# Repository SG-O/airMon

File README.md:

**WARNING** This is work in progress! Expect everything to be broken!

# airMon - ESP32 based air quality monitor PCB #

## Features ##
### CPU ###
- Standard ESP32 WROOM module
- CH340 based USB to UART
- 802.11 b/g/n
- Bluetooth: v4.2 BR/EDR and BLE

### IO ###
- 1 Analog IO port (0 - 12V)
- 1 Analog IO port (0 - 3.3V)
- 2 I2C buses on 4 connectors (2 of which have switchable power pins)
- 2 Additional buffered I2C connectors for longer cables (using P82B715)
- 8 GPIO
- 1 SW bus
- Dedicated connectors for several particulate matter sensors with switchable power pins
 - SDS011
 - PMS1003 - PMS6003
 - PMS7003
- Input for rainfall, wind speed and direction sensors
- GNSS support (L70/L76/MAX-M8C/MAX-M8Q/MAX-8C/MAX-8Q)
- LoRa support (RFM95/RFM96/RFM97/RFM98/RFM69)
- Input voltage measurement
- JTAG for development

### Power Supply ###
- Wide input range (6 - 35V)
- Ultra-high efficiency at light load
- Capable of 5W combined system load
- Overcurrent protection
- Customizable undervoltage protection (for battery operation)
- Switchable power outputs for high power sensors
- Reverse polarity protection

### Additional features ###
- Fits inside a 75mm waste pipe
- PMS7003 can be directly plugged into the PCB
- Active GNSS Antenna support

## Software ##
This was designed for the Airrohr Firmware developed by Opendata Stuttgart: [https://github.com/opendata-stuttgart/sensors-software/tree/master/airrohr-firmware](https://github.com/opendata-stuttgart/sensors-software/tree/master/airrohr-firmware)

The ESP32 support is currently experimental

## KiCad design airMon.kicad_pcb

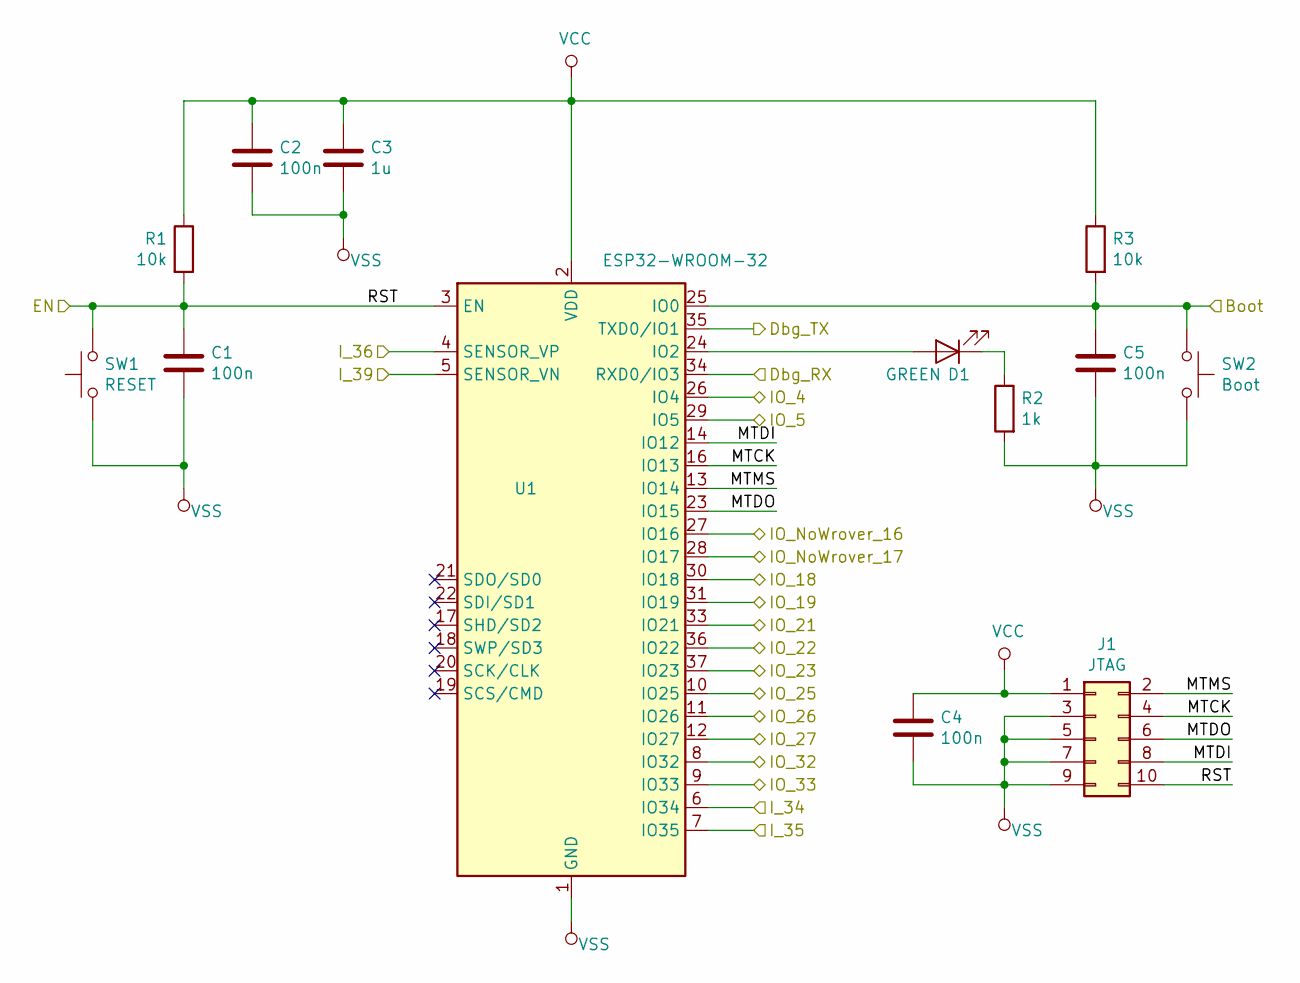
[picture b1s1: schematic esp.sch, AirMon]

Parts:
C1, C2, C4, C5: 100n; C_0603_1608Metric; lcsc# C14663
C3: 1u; C_0805_2012Metric; lcsc# C28323
D1: GREEN; D_0805_2012Metric; lcsc# C2297
J1: JTAG; PinHeader_2x05_P1.27mm_Vertical_SMD; lcsc# C180221
R1, R3: 10k; R_0603_1608Metric; lcsc# C25804
R2: 1k; R_0805_2012Metric; lcsc# C17513
SW1: RESET; SW_SPST_SKQG_WithStem; lcsc# C318889
SW2: Boot; SW_SPST_SKQG_WithStem; lcsc# C318889
U1: ESP32-WROOM-32

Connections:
/A1: U1.6 (IO34); also elsewhere on the board
/A2: U1.7 (IO35); also elsewhere on the board
/A3: U1.4 (SENSOR_VP); also elsewhere on the board
/A4: U1.5 (SENSOR_VN); also elsewhere on the board
/Boot: C5.1, R3.2, SW2.1, U1.25 (IO0); also elsewhere on the board
/EN: C1.1, J1.10, R1.2, SW1.1, U1.3 (EN); also elsewhere on the board
/ESP32/MTCK: J1.4, U1.16 (IO13)
/ESP32/MTDI: J1.8, U1.14 (IO12)
/ESP32/MTDO: J1.6, U1.23 (IO15)
/ESP32/MTMS: J1.2, U1.13 (IO14)
/GPIO_1: U1.37 (IO23); also elsewhere on the board
/GPIO_2: U1.10 (IO25); also elsewhere on the board
/GPIO_3: U1.11 (IO26); also elsewhere on the board
/GPIO_4: U1.12 (IO27); also elsewhere on the board
/GPS_Wake: U1.29 (IO5); also elsewhere on the board
/SCL_1: U1.36 (IO22); also elsewhere on the board
/SCL_2: U1.31 (IO19); also elsewhere on the board
/SDA_1: U1.33 (IO21); also elsewhere on the board
/SDA_2: U1.30 (IO18); also elsewhere on the board
/SW_BUS: U1.26 (IO4); also elsewhere on the board
/U1_RX: U1.8 (IO32); also elsewhere on the board
/U1_TX: U1.9 (IO33); also elsewhere on the board
/U2_RX: U1.27 (IO16); also elsewhere on the board
/U2_TX: U1.28 (IO17); also elsewhere on the board
/U3_RX: U1.34 (RXD0/IO3); also elsewhere on the board
/U3_TX: U1.35 (TXD0/IO1); also elsewhere on the board
unnamed: D1.1 (K), R2.1
unnamed: D1.2 (A), U1.24 (IO2)
VCC: C2.1, C3.1, C4.1, J1.1, R1.1, R3.1, U1.2 (VDD); also elsewhere on the board
VSS: C1.2, C2.2, C3.2, C4.2, C5.2, J1.3, J1.5, J1.7, J1.9, R2.2, SW1.2, SW2.2, U1.1 (GND), U1.15 (GND), U1.38 (GND), U1.39 (GND); also elsewhere on the board

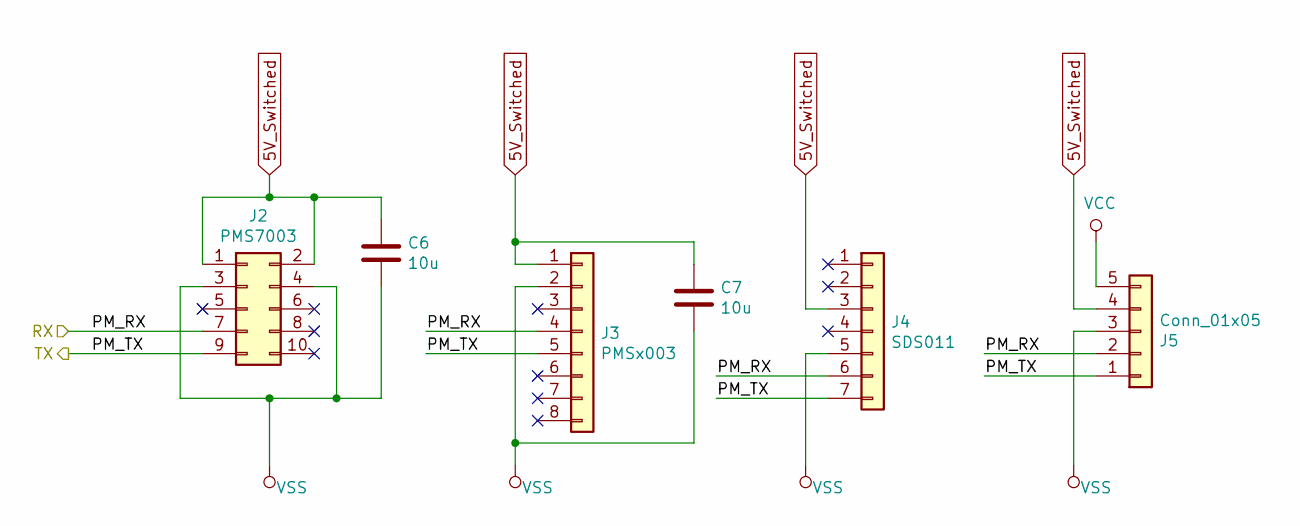
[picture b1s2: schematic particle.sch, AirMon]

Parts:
C6, C7: 10u; C_1206_3216Metric; lcsc# C13585
J2: PMS7003; PinSocket_2x05_P1.27mm_Vertical
J3: PMSx003; Molex_PicoBlade_53047-0810_1x08_P1.25mm_Vertical; lcsc# C240845
J4: SDS011; JST_XH_B07B-XH-A_1x07_P2.50mm_Vertical; lcsc# C144398
J5: Conn_01x05; JST_XH_B05B-XH-A_1x05_P2.50mm_Vertical; lcsc# C157991

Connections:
5V_Switched: C6.1, C7.1, J2.1, J2.2, J3.1, J4.3, J5.4; also elsewhere on the board
/U1_RX: J2.9, J3.5, J4.7, J5.1; also elsewhere on the board
/U1_TX: J2.7, J3.4, J4.6, J5.2; also elsewhere on the board
VCC: J5.5; also elsewhere on the board
VSS: C6.2, C7.2, J2.3, J2.4, J3.2, J4.5, J5.3; also elsewhere on the board

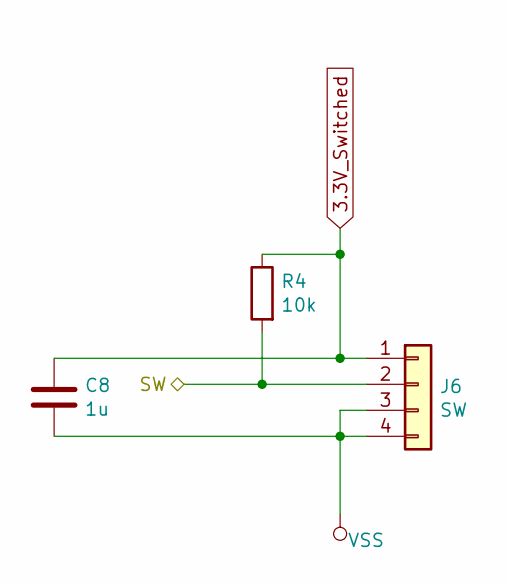
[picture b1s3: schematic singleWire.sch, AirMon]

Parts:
C8: 1u; C_0805_2012Metric; lcsc# C28323
J6: SW; PinSocket_1x04_P2.54mm_Vertical
R4: 10k; R_0603_1608Metric; lcsc# C25804

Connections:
3.3V_Switched: C8.1, J6.1, R4.1; also elsewhere on the board
/SW_BUS: J6.2, R4.2; also elsewhere on the board
VSS: C8.2, J6.3, J6.4; also elsewhere on the board

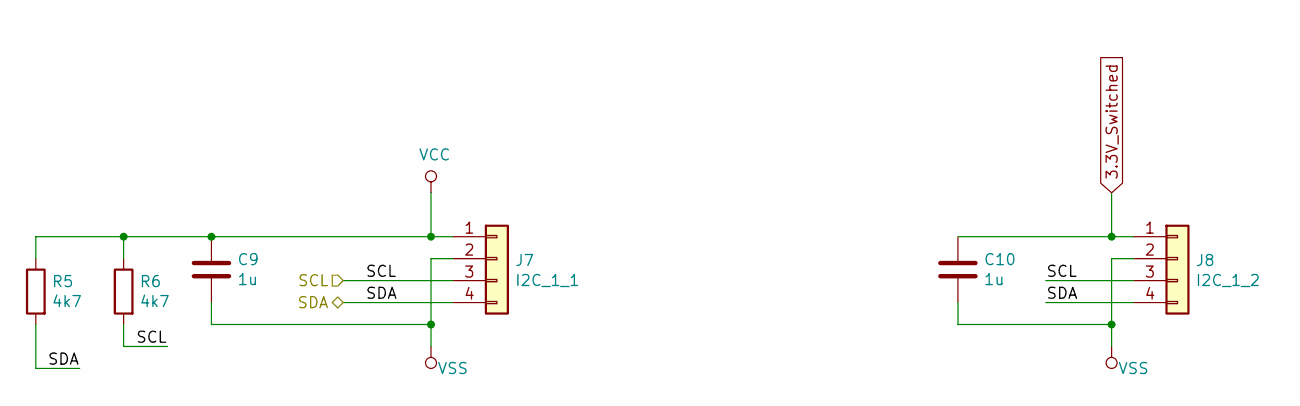
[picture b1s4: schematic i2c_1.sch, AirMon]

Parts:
C9, C10: 1u; C_0805_2012Metric; lcsc# C28323
J7: I2C_1_1; PinSocket_1x04_P2.54mm_Vertical
J8: I2C_1_2; PinSocket_1x04_P2.54mm_Vertical
R5, R6: 4k7; R_0603_1608Metric; lcsc# C23162

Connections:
3.3V_Switched: C10.1, J8.1; also elsewhere on the board
/SCL_1: J7.3, J8.3, R6.2; also elsewhere on the board
/SDA_1: J7.4, J8.4, R5.2; also elsewhere on the board
VCC: C9.1, J7.1, R5.1, R6.1; also elsewhere on the board
VSS: C9.2, C10.2, J7.2, J8.2; also elsewhere on the board

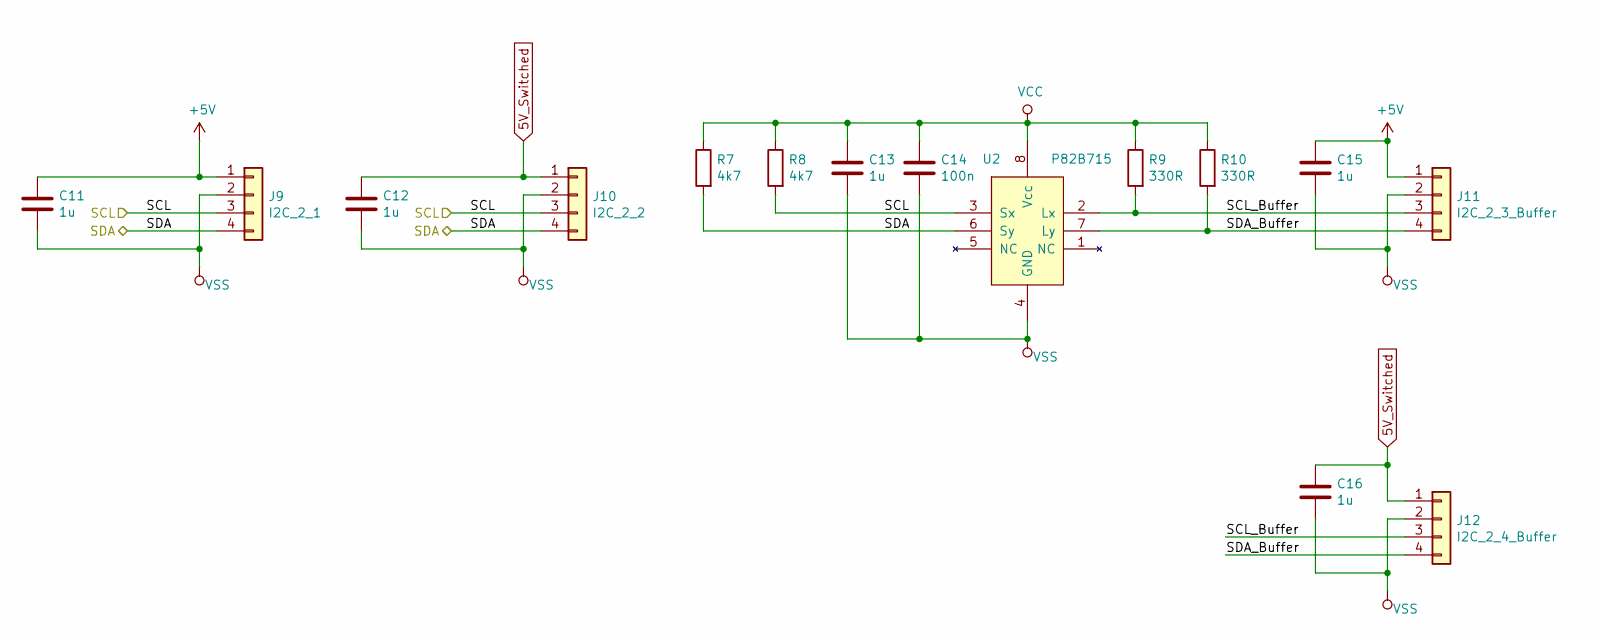
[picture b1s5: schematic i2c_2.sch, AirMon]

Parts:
C11, C12, C13, C15, C16: 1u; C_0805_2012Metric; lcsc# C28323
C14: 100n; C_0603_1608Metric; lcsc# C14663
J9: I2C_2_1; PinSocket_1x04_P2.54mm_Vertical
J10: I2C_2_2; PinSocket_1x04_P2.54mm_Vertical
J11: I2C_2_3_Buffer; PinSocket_1x04_P2.54mm_Vertical
J12: I2C_2_4_Buffer; PinSocket_1x04_P2.54mm_Vertical
R7, R8: 4k7; R_0603_1608Metric; lcsc# C23162
R9, R10: 330R; R_0603_1608Metric; lcsc# C23138
U2: P82B715; SOIC-8_3.9x4.9mm_P1.27mm; digikey# 296-24729-1-ND

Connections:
5V_Switched: C12.1, C16.1, J10.1, J12.1; also elsewhere on the board
+5V: C11.1, C15.1, J9.1, J11.1; also elsewhere on the board
/I2C_2/SCL_Buffer: J11.3, J12.3, R9.2, U2.2 (Lx)
/I2C_2/SDA_Buffer: J11.4, J12.4, R10.2, U2.7 (Ly)
/SCL_2: J9.3, J10.3, R8.2, U2.3 (Sx); also elsewhere on the board
/SDA_2: J9.4, J10.4, R7.2, U2.6 (Sy); also elsewhere on the board
VCC: C13.1, C14.1, R7.1, R8.1, R9.1, R10.1, U2.8 (Vcc); also elsewhere on the board
VSS: C11.2, C12.2, C13.2, C14.2, C15.2, C16.2, J9.2, J10.2, J11.2, J12.2, U2.4 (GND); also elsewhere on the board

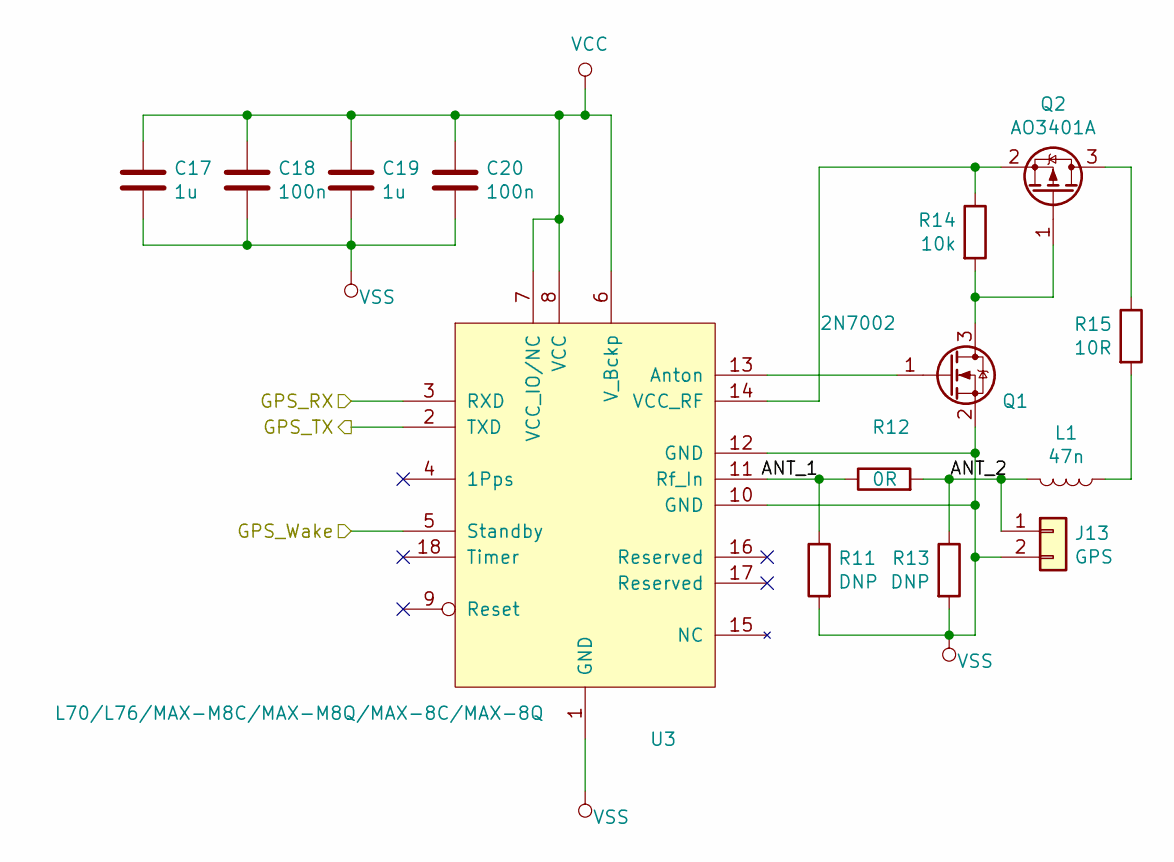
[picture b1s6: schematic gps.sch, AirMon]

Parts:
C17, C19: 1u; C_0805_2012Metric; lcsc# C28323
C18, C20: 100n; C_0603_1608Metric; lcsc# C14663
J13: GPS; U.FL_Molex_MCRF_73412-0110_Vertical; lcsc# C88374
L1: 47n; L_0603_1608Metric; lcsc# C29683
Q1: 2N7002; SOT-23; lcsc# C8545
Q2: AO3401A; SOT-23; lcsc# C15127
R11, R13: DNP; R_0603_1608Metric
R12: 0R; R_0603_1608Metric; lcsc# C21189
R14: 10k; R_0603_1608Metric; lcsc# C25804
R15: 10R; R_0603_1608Metric; lcsc# C22859
U3: L70/L76/MAX-M8C/MAX-M8Q/MAX-8C/MAX-8Q; L70

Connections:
/GPS/ANT_1: R11.1, R12.1, U3.11 (Rf_In)
/GPS/ANT_2: J13.1, L1.2, R12.2, R13.1
/GPS_Wake: U3.5 (Standby); also elsewhere on the board
/U2_RX: U3.2 (TXD); also elsewhere on the board
/U2_TX: U3.3 (RXD); also elsewhere on the board
unnamed: L1.1, R15.2
unnamed: Q1.1 (G), U3.13 (Anton)
unnamed: Q1.3 (D), Q2.1 (G), R14.2
unnamed: Q2.2 (S), R14.1, U3.14 (VCC_RF)
unnamed: Q2.3 (D), R15.1
VCC: C17.1, C18.1, C19.1, C20.1, U3.6 (V_Bckp), U3.7 (VCC_IO/NC), U3.8 (VCC); also elsewhere on the board
VSS: C17.2, C18.2, C19.2, C20.2, J13.2, Q1.2 (S), R11.2, R13.2, U3.1 (GND), U3.10 (GND), U3.12 (GND); also elsewhere on the board

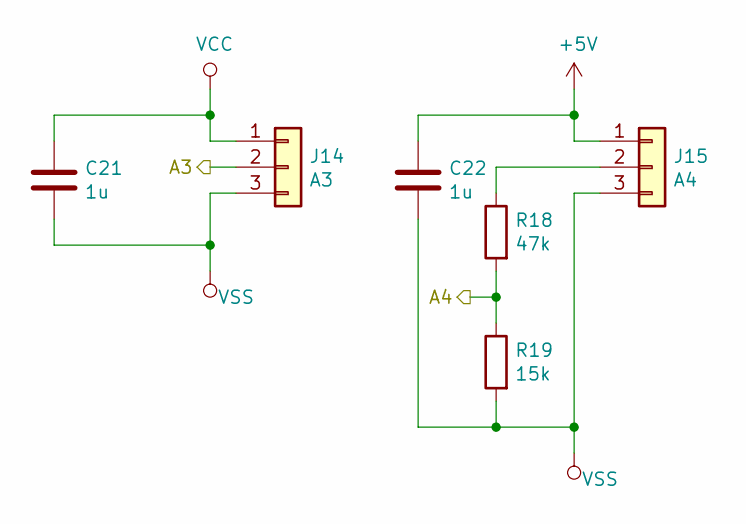
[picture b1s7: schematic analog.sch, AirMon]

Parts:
C21, C22: 1u; C_0805_2012Metric; lcsc# C28323
J14: A3; PinSocket_1x03_P2.54mm_Vertical
J15: A4; PinSocket_1x03_P2.54mm_Vertical
R18: 47k; R_0603_1608Metric; lcsc# C25819
R19: 15k; R_0603_1608Metric; lcsc# C22809

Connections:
+5V: C22.1, J15.1; also elsewhere on the board
/A3: J14.2; also elsewhere on the board
/A4: R18.2, R19.1; also elsewhere on the board
unnamed: J15.2, R18.1
VCC: C21.1, J14.1; also elsewhere on the board
VSS: C21.2, C22.2, J14.3, J15.3, R19.2; also elsewhere on the board

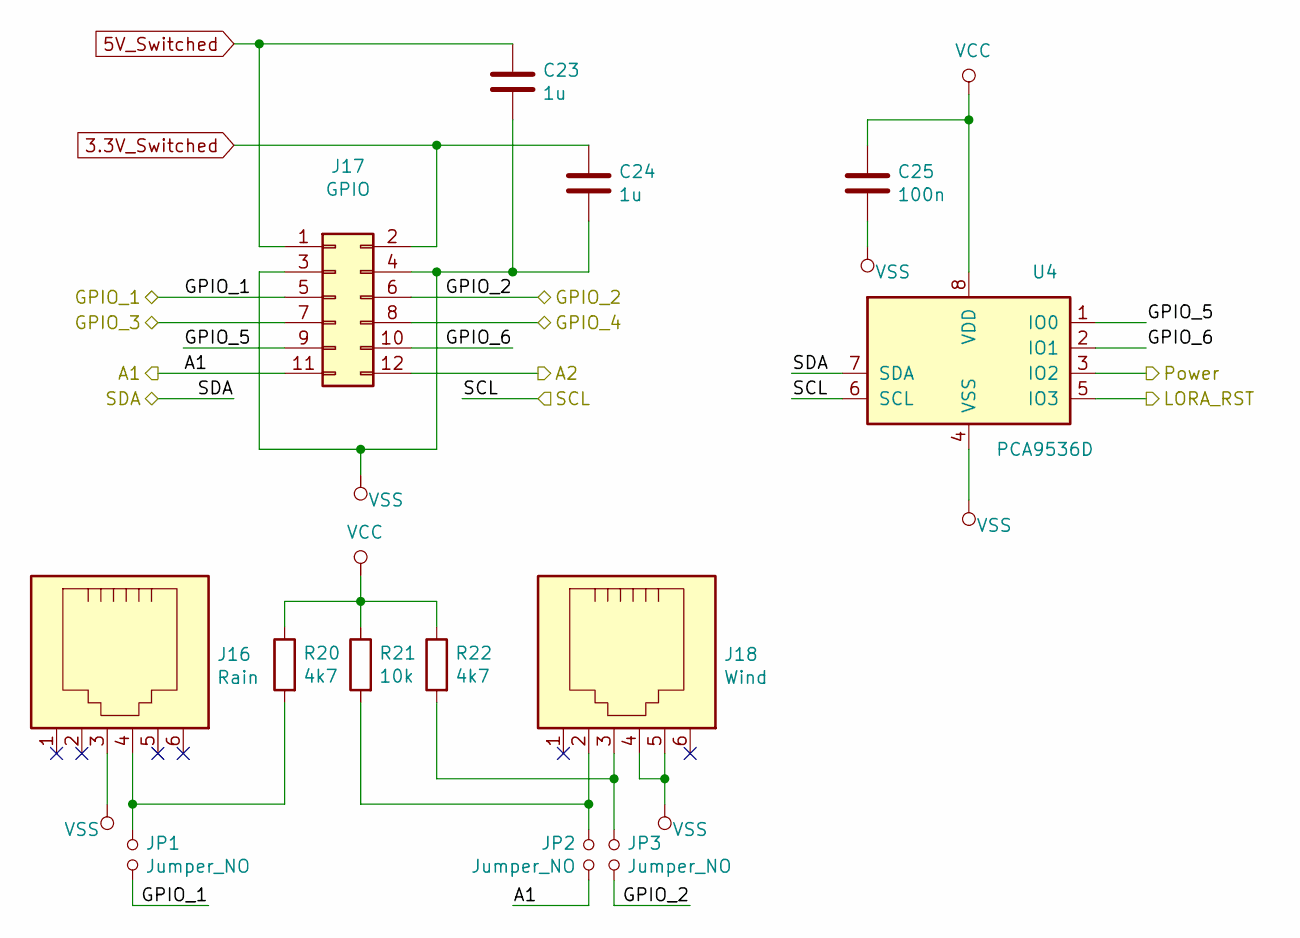
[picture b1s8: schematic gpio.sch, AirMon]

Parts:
C23, C24: 1u; C_0805_2012Metric; lcsc# C28323
C25: 100n; C_0603_1608Metric; lcsc# C14663
J16: Rain; DS1133-S60; lcsc# C77856
J17: GPIO; PinHeader_2x06_P2.54mm_Vertical
J18: Wind; DS1133-S60; lcsc# C77856
JP1, JP2, JP3: Jumper_NO; PinHeader_1x02_P2.54mm_Vertical
R20, R22: 4k7; R_0603_1608Metric; lcsc# C23162
R21: 10k; R_0603_1608Metric; lcsc# C25804
U4: PCA9536D; SOIC-8_3.9x4.9mm_P1.27mm; lcsc# C129522

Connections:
3.3V_Switched: C24.1, J17.2; also elsewhere on the board
5V_Switched: C23.1, J17.1; also elsewhere on the board
/A1: J17.11, JP2.2; also elsewhere on the board
/A2: J17.12; also elsewhere on the board
/GPIO/GPIO_5: J17.9, U4.1 (IO0)
/GPIO/GPIO_6: J17.10, U4.2 (IO1)
/GPIO_1: J17.5, JP1.2; also elsewhere on the board
/GPIO_2: J17.6, JP3.2; also elsewhere on the board
/GPIO_3: J17.7; also elsewhere on the board
/GPIO_4: J17.8; also elsewhere on the board
/LORA_RST: U4.5 (IO3); also elsewhere on the board
/POWER: U4.3 (IO2); also elsewhere on the board
/SCL_1: U4.6 (SCL); also elsewhere on the board
/SDA_1: U4.7 (SDA); also elsewhere on the board
unnamed: J16.4, JP1.1, R20.2
unnamed: J18.2, JP2.1, R21.2
unnamed: J18.3, JP3.1, R22.2
VCC: C25.1, R20.1, R21.1, R22.1, U4.8 (VDD); also elsewhere on the board
VSS: C23.2, C24.2, C25.2, J16.3, J17.3, J17.4, J18.4, J18.5, U4.4 (VSS); also elsewhere on the board

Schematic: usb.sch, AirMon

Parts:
C26: 10u; C_1206_3216Metric; lcsc# C13585
C27, C28: 100n; C_0603_1608Metric; lcsc# C14663
F1: Polyfuse; Fuse_0603_1608Metric; lcsc# C207014
J19: USB_B_Micro; USB_Micro-B_Molex-105017-0001; lcsc# C136000
Q3, Q4: SS8050; SOT-23; lcsc# C2150
R23, R24: 470R; R_0603_1608Metric; lcsc# C23179
R25, R26: 10k; R_0603_1608Metric; lcsc# C25804
U5: CH340C; SOIC-16_3.9x9.9mm_P1.27mm; lcsc# C84681

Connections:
/Boot: Q4.3 (C); also elsewhere on the board
/EN: Q3.3 (C); also elsewhere on the board
/U3_RX: R24.2; also elsewhere on the board
/U3_TX: R23.2; also elsewhere on the board
/USB/DTR: Q4.2 (E), R25.1, U5.13 (~DTR)
/USB/RTS: Q3.2 (E), R26.1, U5.14 (~RTS)
unnamed: C26.1, F1.2, J19.1 (VBUS)
unnamed: C27.1, U5.4 (V3)
unnamed: J19.2 (D-), U5.6 (UD-)
unnamed: J19.3 (D+), U5.5 (UD+)
unnamed: Q3.1 (B), R25.2
unnamed: Q4.1 (B), R26.2
unnamed: R23.1, U5.3 (RXD)
unnamed: R24.1, U5.2 (TXD)
VBUS: F1.1; also elsewhere on the board
VCC: C28.1, U5.16 (VCC); also elsewhere on the board
VSS: C26.2, C27.2, C28.2, J19.5 (GND), J19.6 (Shield), U5.1 (GND); also elsewhere on the board

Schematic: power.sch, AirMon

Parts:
C29, C31, C32, C34: 10u; C_1206_3216Metric; lcsc# C13585
C30, C33: 100n; C_0603_1608Metric; lcsc# C14663
D2, D5: SK36A-LTP; D_SMA; digikey# SK36A-LTPMSCT-ND
D3, D4: BAT760-7; D_SOD-323; lcsc# C124187
D6: UDZVTE-1712B; D_SOD-323F; lcsc# C84980
J20: Power; TerminalBlock_bornier-2_P5.08mm; lcsc# C8475
JP4: Jumper_NO; PinHeader_1x02_P2.54mm_Vertical
L2: 22uH; L_Bourns_SRN8040; digikey# SRN8040-220MCT-ND
L3: 15uH; L_Bourns_SRN6045TA; digikey# SRN6045-150MCT-ND
Q5, Q7: 2N7002; SOT-23; lcsc# C8545
Q6, Q8, Q9: DMP6023LE-13; SOT-223-3_TabPin2; lcsc# C154901
R27, R28: DNP; R_Axial_DIN0204_L3.6mm_D1.6mm_P7.62mm_Horizontal
R29, R34, R36: 110k; R_0603_1608Metric; lcsc# C326736
R30, R32, R33: 100k; R_0603_1608Metric; lcsc# C25803
R31: 10k; R_0603_1608Metric; lcsc# C25804
R35: 20k; R_0603_1608Metric; lcsc# C191225
R37: 33k; R_0603_1608Metric; lcsc# C416700
R38: 1M; R_0603_1608Metric; lcsc# C22935
U6, U7: LMR14010ADDCR; TSOT-23-6; lcsc# C388174

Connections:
3.3V_Switched: Q8.2 (D); also elsewhere on the board
5V_Switched: Q6.2 (D); also elsewhere on the board
+5V: C31.1, D4.2 (A), L2.1, Q6.3 (S), R30.1, R34.1; also elsewhere on the board
+VDC: C29.1, D6.1 (K), Q9.3 (S), R27.1, R29.1, U6.5 (VIN)
/A3: JP4.1; also elsewhere on the board
/POWER: Q5.1 (G), Q7.1 (G), R32.2; also elsewhere on the board
unnamed: C30.1, U6.1 (CB)
unnamed: C30.2, D2.1 (K), L2.2, U6.6 (SW)
unnamed: C32.1, D3.1 (K), D4.1 (K), U7.4 (~SHDN), U7.5 (VIN)
unnamed: C33.1, U7.1 (CB)
unnamed: C33.2, D5.1 (K), L3.2, U7.6 (SW)
unnamed: D6.2 (A), Q9.1 (G), R38.1
unnamed: J20.1, Q9.2 (D)
unnamed: JP4.2, R29.2, R31.1
unnamed: Q5.3 (D), Q6.1 (G), R30.2
unnamed: Q7.3 (D), Q8.1 (G), R33.2
unnamed: R27.2, R28.1, U6.4 (~SHDN)
unnamed: R34.2, R35.1, U6.3 (FB)
unnamed: R36.2, R37.1, U7.3 (FB)
VBUS: D3.2 (A); also elsewhere on the board
VCC: C34.1, L3.1, Q8.3 (S), R33.1, R36.1; also elsewhere on the board
VSS: C29.2, C31.2, C32.2, C34.2, D2.2 (A), D5.2 (A), J20.2, Q5.2 (S), Q7.2 (S), R28.2, R31.2, R32.1, R35.2, R37.2, R38.2, U6.2 (GND), U7.2 (GND); also elsewhere on the board

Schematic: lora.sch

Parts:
C35: 1u; C_0805_2012Metric; lcsc# C28323
J21: LORA_1; U.FL_Molex_MCRF_73412-0110_Vertical; lcsc# C88374
J22: LORA_2; PinHeader_1x02_P1.27mm_Vertical
JP5: Mode; SolderJumper-3_P1.3mm_Bridged12_RoundedPad1.0x1.5mm_NumberL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
R39, R41: DNP; R_0603_1608Metric
R40: 0R; R_0603_1608Metric; lcsc# C21189
U8: RFM95W-868S2; HOPERF_RFM9XW_SMD

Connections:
/A1: U8.14 (DIO0); also elsewhere on the board
/A2: JP5.2 (C); also elsewhere on the board
/GPIO_1: U8.3 (MOSI); also elsewhere on the board
/GPIO_2: U8.2 (MISO); also elsewhere on the board
/GPIO_3: U8.4 (SCK); also elsewhere on the board
/GPIO_4: U8.5 (NSS); also elsewhere on the board
/LORA/ANT_1: R39.1, R40.1, U8.9 (ANT)
/LORA/ANT_2: J21.1, J22.1, R40.2, R41.1
/LORA_RST: U8.6 (RESET); also elsewhere on the board
unnamed: JP5.1 (A), U8.15 (DIO1)
unnamed: JP5.3 (B), U8.16 (DIO2)
VCC: C35.1, U8.13 (3.3V); also elsewhere on the board
VSS: C35.2, J21.2, J22.2, R39.2, R41.2, U8.1 (GND), U8.8 (GND), U8.10 (GND); also elsewhere on the board

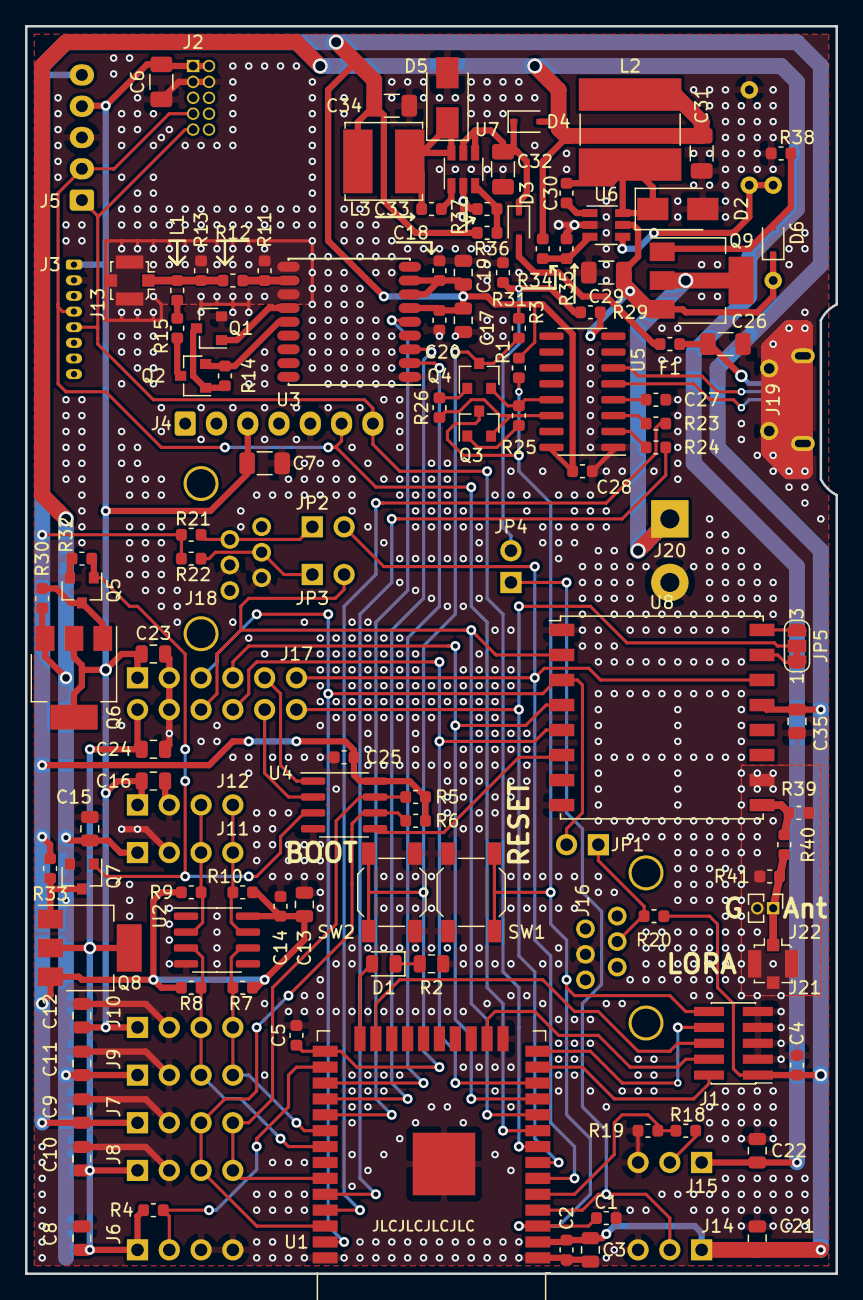
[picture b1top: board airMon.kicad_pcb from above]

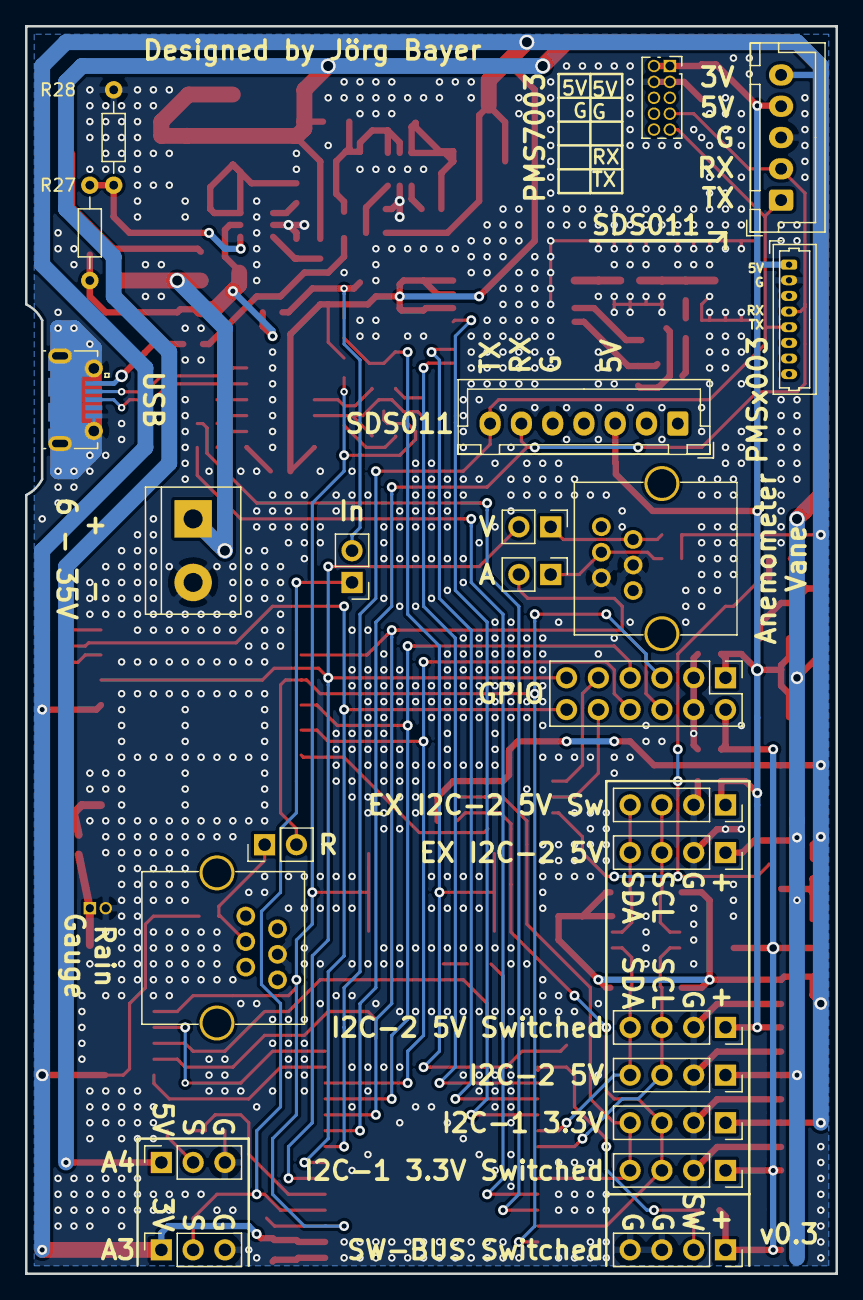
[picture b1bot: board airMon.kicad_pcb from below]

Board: 2 copper layers, 64.8 x 99.7 mm, 130 parts (24 on the bottom side), 79 nets.

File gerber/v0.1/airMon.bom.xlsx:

Comment | Designator | Footprint | LCSC Part #（optional）
100n | C1 C2 C4 C5 C14 C18 C20 C25 C27 C28 C30 C33 | C_0603_1608Metric | C14663
10u | C6 C7 C26 C29 C31 C32 C34 | C_1206_3216Metric | C13585
1u | C3 C8 C9 C10 C11 C12 C13 C15 C16 C17 C19 C21 C22 C23 C24 | C_0805_2012Metric | C28323
BAT760-7 | D3 D4 | D_SOD-323 | C124187
GREEN | D1 | D_0805_2012Metric | C2297
UDZVTE-1712B | D6 | D_SOD-323F | C84980
Polyfuse | F1 | Fuse_0603_1608Metric | C207014
Conn_01x05 | J5 | JST_XH_B05B-XH-A_1x05_P2.50mm_Vertical | C157991
GPS | J13 | U.FL_Molex_MCRF_73412-0110_Vertical | C88374
PMSx003 | J3 | Molex_PicoBlade_53047-0810_1x08_P1.25mm_Vertical | C240845
Power | J20 | TerminalBlock_bornier-2_P5.08mm | C8475
Rain | J16 | DS1133-S60 | C77856
SDS011 | J4 | JST_XH_B07B-XH-A_1x07_P2.50mm_Vertical | C144398
USB_B_Micro | J19 | USB_Micro-B_Molex-105017-0001 | C136000
Wind | J18 | DS1133-S60 | C77856
47n | L1 | L_0603_1608Metric | C29683
2N7002 | Q1 Q5 Q7 | SOT-23 | C8545
AO3401A | Q2 | SOT-23 | C15127
DMP6023LE-13 | Q6 Q8 Q9 | SOT-223-3_TabPin2 | C154901
SS8050 | Q3 Q4 | SOT-23 | C2150
0R | R12 | R_0603_1608Metric | C21189
100k | R30 R32 R33 | R_0603_1608Metric | C25803
10R | R15 | R_0603_1608Metric | C22859
10k | R1 R3 R4 R14 R21 R25 R26 R31 | R_0603_1608Metric | C25804
110k | R29 R34 R36 | R_0603_1608Metric | C326736
15k | R17 R19 | R_0603_1608Metric | C22809
1M | R38 | R_0603_1608Metric | C22935
1k | R2 | R_0805_2012Metric | C17513
20k | R35 | R_0603_1608Metric | C191225
330R | R9 R10 | R_0603_1608Metric | C23138
33k | R37 | R_0603_1608Metric | C416700
470R | R23 R24 | R_0603_1608Metric | C23179
47k | R16 R18 | R_0603_1608Metric | C25819
4k7 | R5 R6 R7 R8 R20 R22 | R_0603_1608Metric | C23162
Boot | SW2 | SW_SPST_SKQG_WithStem | C318889
RESET | SW1 | SW_SPST_SKQG_WithStem | C318889
CH340C | U5 | SOIC-16_3.9x9.9mm_P1.27mm | C84681
LMR14010ADDCR | U6 U7 | TSOT-23-6 | C388174
PCA9536D | U4 | SOIC-8_3.9x4.9mm_P1.27mm | C129522

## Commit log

2020-01-13 Add LICENSE
2020-01-13 Added images Added information to schematic Added information to layout
2020-01-14 Added Readme Added GNSS receiver list Fixed GNSS receiver connections Improved Pictures
2020-01-14 Added Firmware link
2020-01-14 Added gerber files Added schematic pdf
2020-01-14 Reduced image size
2020-01-14 Added reverse polarity protection Improved power switch mosfets
2020-01-14 Added reverse polarity protection Changed power switch MOSFETs to a lower RDS(on) model Improved buck converter layout Improved USB layout
2020-01-15 Fixed reverse polarity protection
2020-01-16 Added fuse for USB Added buttons for boot and reset Added version number to PCB Changed several component values for improved manufacturing Added BOM Added component position file
2020-01-16 Moved to KiCad 5.1.5_3
2020-01-16 Release v0.1 Added contributing guidelines
2020-01-16 Added issue templates
2020-01-16 Update issue templates
2020-01-16 Added pull request template
2020-01-16 Changed pull request template directory
2020-01-17 Start of v0.2 Updated footprints
2020-01-17 Made PMS7003 footprint virtual
2020-01-17 Updated images
2020-01-19 Added RFM95 Module for Lora Added Changelog Changed input voltage monitoring from A2(IO35) to A3(IO36) Removed A3 12V compatibility Rearranged IOs to fit new components
2020-01-19 Added updated schematic Added updated gerber Updated date
2020-03-06 Swaped two wrong I2C signals.
2020-03-06 Release v0.3

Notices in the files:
airMon.kicad_pcb:
CC BY 4.0
